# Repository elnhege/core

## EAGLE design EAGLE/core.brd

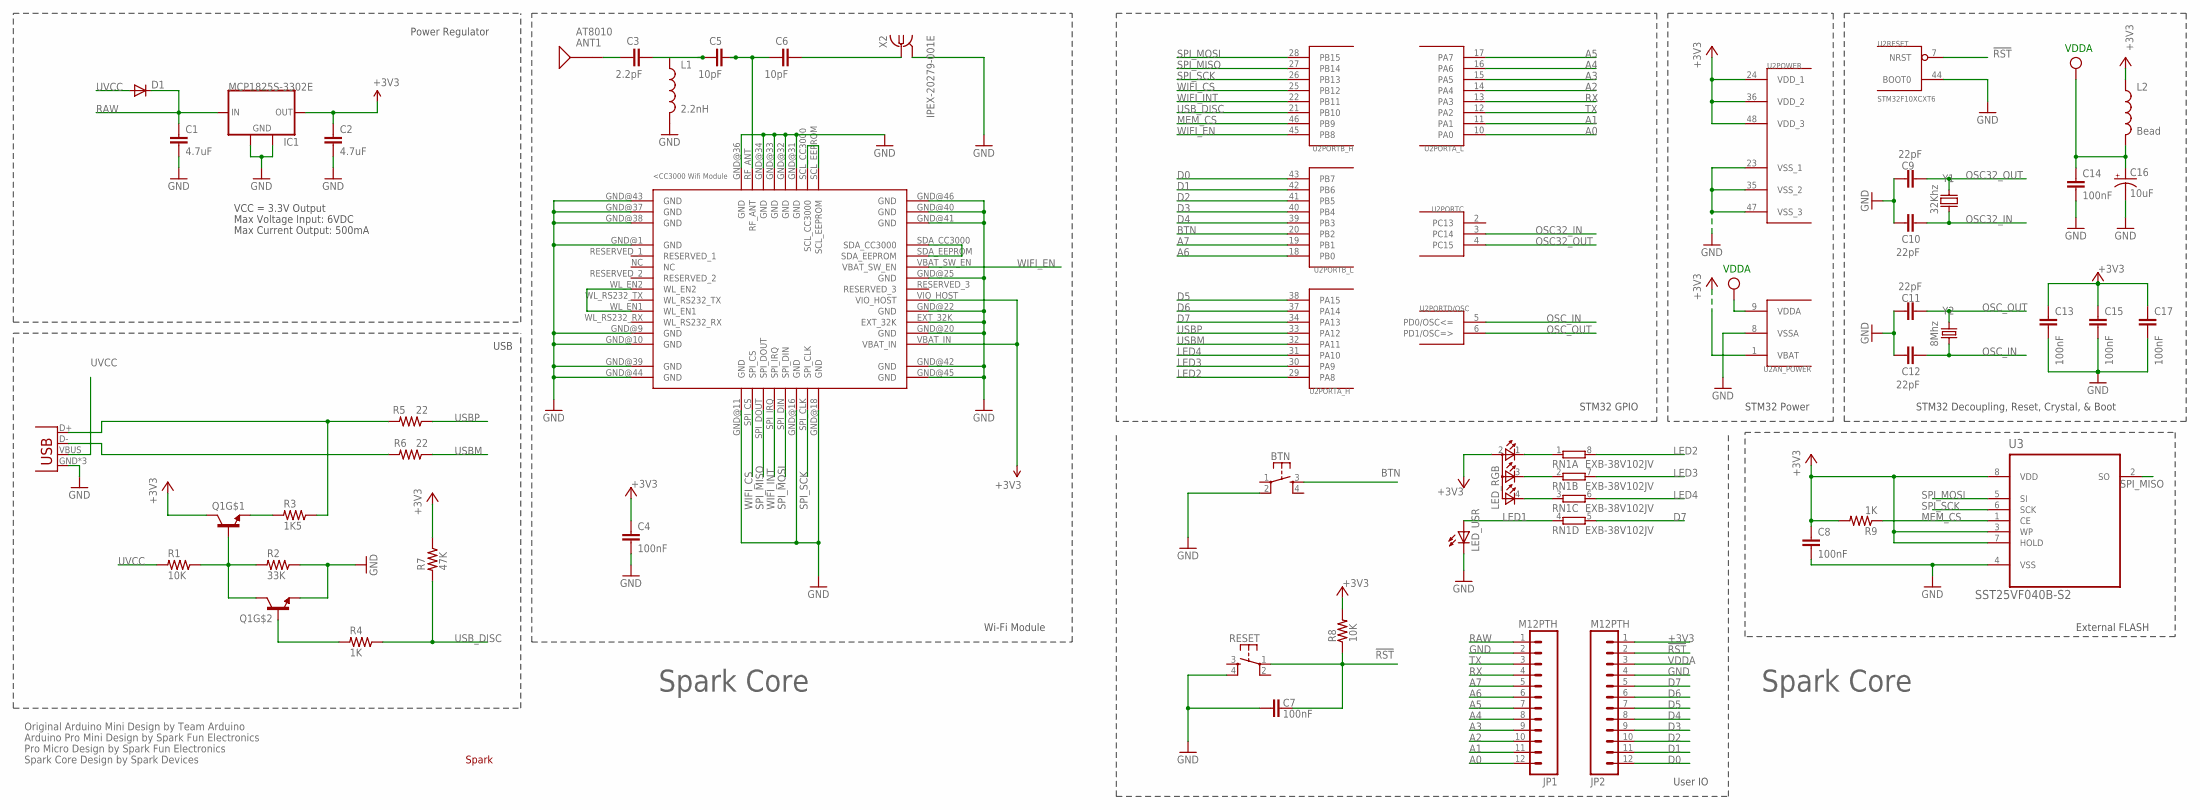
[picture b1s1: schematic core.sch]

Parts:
ANT1: AT8010
BTN: KMR211GLFS; TACTILE_SWITCH_SMD
C1, C2: 4.7uF; C0603
C3: 2.2pF; C0603
C4, C7, C8, C13, C14, C15, C17: 100nF; C0603
C5, C6: 10pF; C0603
C9, C10, C11, C12: 22pF; C0603
C16: 10uF; EIA3216
D1: DIODESOD; SOD-323
IC1: MCP1825S-3302E; SOT223
JP1, JP2: M12PTH; 1X12-SMALL-PADS
L1: 2.2nH; 0603
L2: Bead; 0603
LED_RGB: TOPLED-3PLCC; P-LCC-4-3
LED_USR: LED0603; LED-0603
Q1: MMDT3904; SOT363
R1, R8: 10K; R0603
R2: 33K; R0603
R3: 1K5; R0603
R4, R9: 1K; R0603
R5, R6: 22; R0603
R7: 47K; R0603
RESET: KMR211GLFS; TACTILE_SWITCH_SMD
RN1: EXB-38V102JV; EXB38V
U1: CC3000
U2: STM32F10XCXT6; TQFP48
U3: SST25VF040B-S2; SOIC127P790X216-8N
U$1: SPARK_LOGO2
X1: USB-MICROB; USB-MICROB-SLOT-HOLE
X2: IPEX-20279-001E
Y1: 32Khz; FC135
Y2: 8Mhz; CRYSTAL-SMD-5X3

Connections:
!RST: C7.2, JP2.2, R8.1, RESET.1, U2.7 (NRST)
+3V3: C2.1, C4.1, C8.1, C13.1, C15.1, C17.1, IC1.3 (OUT), JP2.1, L2.1, LED_RGB.2 (A2), Q1.3 (C), R7.1, R8.2, R9.2, U1.VBAT_IN, U1.VIO_HOST, U2.1 (VBAT), U2.24 (VDD_1), U2.36 (VDD_2), U2.48 (VDD_3), U3.3 (WP), U3.7 (HOLD), U3.8 (VDD)
A0: JP1.12, U2.10 (PA0)
A1: JP1.11, U2.11 (PA1)
A2: JP1.10, U2.14 (PA4)
A3: JP1.9, U2.15 (PA5)
A4: JP1.8, U2.16 (PA6)
A5: JP1.7, U2.17 (PA7)
A6: JP1.6, U2.18 (PB0)
A7: JP1.5, U2.19 (PB1)
BTN: BTN.3, U2.20 (PB2)
D0: JP2.12, U2.43 (PB7)
D1: JP2.11, U2.42 (PB6)
D2: JP2.10, U2.41 (PB5)
D3: JP2.9, U2.40 (PB4)
D4: JP2.8, U2.39 (PB3)
D5: JP2.7, U2.38 (PA15)
D6: JP2.6, U2.37 (PA14)
D7: JP2.5, RN1.5 (2), U2.34 (PA13)
GND: BTN.2, C1.2, C2.2, C4.2, C7.1, C8.2, C9.2, C10.2, C11.2, C12.2, C13.2, C14.2, C15.2, C16.C (-), C17.2, IC1.2 (GND), IC1.4 (GND), JP1.2, JP2.4, L1.2, LED_USR.C, Q1.1 (E), R2.1, RESET.4, U1.EXT_32K, U1.GND@1 (GND), U1.GND@9 (GND), U1.GND@10 (GND), U1.GND@11 (GND), U1.GND@16 (GND), U1.GND@18 (GND), U1.GND@20 (GND), U1.GND@22 (GND), U1.GND@25 (GND), U1.GND@31 (GND), U1.GND@32 (GND), U1.GND@33 (GND), U1.GND@34 (GND), U1.GND@36 (GND), U1.GND@37 (GND), U1.GND@38 (GND), U1.GND@39 (GND), U1.GND@40 (GND), U1.GND@41 (GND), U1.GND@42 (GND), U1.GND@43 (GND), U1.GND@44 (GND), U1.GND@45 (GND), U1.GND@46 (GND), U2.8 (VSSA), U2.23 (VSS_1), U2.35 (VSS_2), U2.44 (BOOT0), U2.47 (VSS_3), U3.4 (VSS), X1.GND, X1.MT1 (GND), X1.MT2 (GND), X2.2@1 (GND), X2.2@2 (GND)
LED1: LED_USR.A, RN1.4 (1)
LED2: RN1.8 (2), U2.29 (PA8)
LED3: RN1.7 (2), U2.30 (PA9)
LED4: RN1.6 (2), U2.31 (PA10)
MEM_CS: R9.1, U2.46 (PB9), U3.1 (CE)
unnamed: R3.1, R5.2, X1.D+
unnamed: C6.2, X2.1
unnamed: ANT1.SIG, C3.1
unnamed: C5.2, C6.1, U1.RF_ANT
unnamed: C3.2, C5.1, L1.1
unnamed: R6.2, X1.D-
unnamed: U1.SCL_CC3000, U1.SCL_EEPROM
unnamed: Q1.2 (B), R4.2
unnamed: U1.WL_EN1, U1.WL_EN2
unnamed: LED_RGB.1 (CRED), RN1.1
unnamed: LED_RGB.3 (CBLUE), RN1.2 (1)
unnamed: Q1.5 (B), Q1.6 (C), R1.1, R2.2
unnamed: LED_RGB.4 (CGREEN), RN1.3 (1)
unnamed: U1.SDA_CC3000, U1.SDA_EEPROM
unnamed: Q1.4 (E), R3.2
OSC32_IN: C10.1, U2.3 (PC14), Y1.X1 (1)
OSC32_OUT: C9.1, U2.4 (PC15), Y1.X2 (2)
OSC_IN: C12.1, U2.5 (PD0/OSC<=), Y2.1
OSC_OUT: C11.1, U2.6 (PD1/OSC=>), Y2.3 (2)
RAW: C1.1, D1.1 (C), IC1.1 (IN), JP1.1
RX: JP1.4, U2.13 (PA3)
SPI_MISO: U1.SPI_DOUT, U2.27 (PB14), U3.2 (SO)
SPI_MOSI: U1.SPI_DIN, U2.28 (PB15), U3.5 (SI)
SPI_SCK: U1.SPI_CLK, U2.26 (PB13), U3.6 (SCK)
TX: JP1.3, U2.12 (PA2)
USBM: R6.1, U2.32 (PA11)
USBP: R5.1, U2.33 (PA12)
USB_DISC: R4.1, R7.2, U2.21 (PB10)
UVCC: D1.2 (A), R1.2, X1.VBUS
VDDA: C14.1, C16.A (+), JP2.3, L2.2, U2.9 (VDDA)
WIFI_CS: U1.SPI_CS, U2.25 (PB12)
WIFI_EN: U1.VBAT_SW_EN, U2.45 (PB8)
WIFI_INT: U1.SPI_IRQ, U2.22 (PB11)

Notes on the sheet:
Original Arduino Mini Design by Team Arduino
Arduino Pro Mini Design by Spark Fun Electronics
Max Voltage Input: 6VDC
Max Current Output: 500mA
Power Regulator
VCC = 3.3V Output
Pro Micro Design by Spark Fun Electronics
Spark Core Design by Spark Devices
STM32 Decoupling, Reset, Crystal, & Boot
STM32 GPIO
STM32 Power
External FLASH
User IO
USB
Spark Core
Wi-Fi Module
VDDA

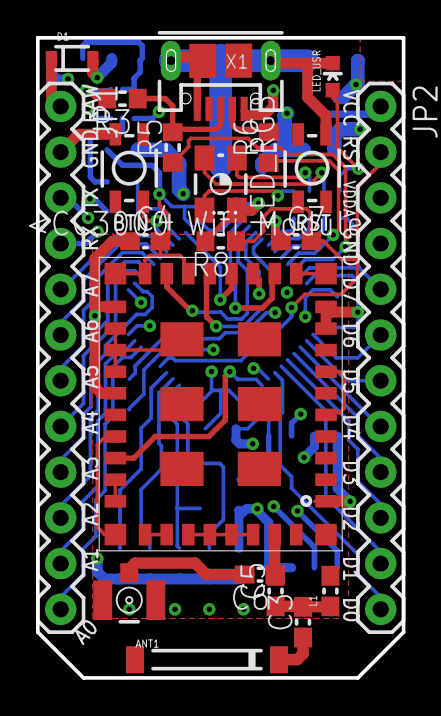
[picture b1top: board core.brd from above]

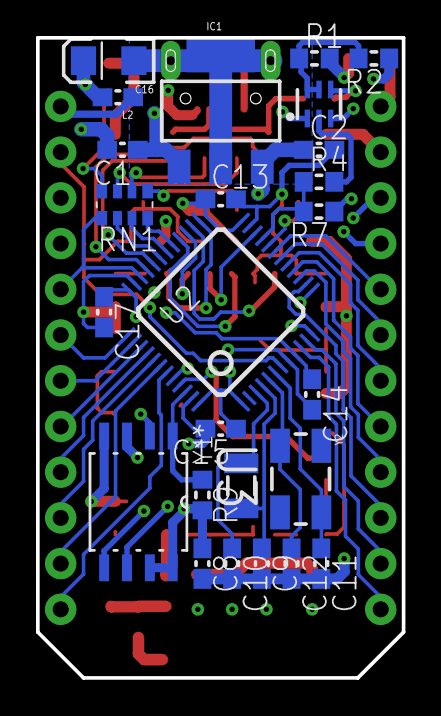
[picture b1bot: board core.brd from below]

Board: 4 copper layers, 20.3 x 35.6 mm, 47 parts (25 on the bottom side), 58 nets.

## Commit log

2013-08-05 Shifted Core board up and created mounting files
2013-08-06 Fixed RGB LED Silkscreen
2013-08-07 added DIODE lib
2013-08-07 updated diode footprint

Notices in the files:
parts and their libraries:
SparkFun-Passives: Licensing: CC v3.0 Share-Alike You are welcome to use this library for commercial purposes.
